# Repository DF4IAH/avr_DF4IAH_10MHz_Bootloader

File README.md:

# avr_DF4IAH_Bootloader

## GPS disciplined 10 MHz reference oscillator based on a (VC)TCXO
The project name for this device is __10 MHz-Ref.-Osc. V2.x__

That board is attached at the USB bus and receives power and does communication over it.
An optional LCD module can be connected to the I²C compatible bus for a stand-alone operation.

The author is Ulrich Habel (DF4IAH) with the idea having a low-cost and low-power device for a module to generate a 10 MHz signal at 3.3V TTL, that is adjusted to the GPS/Glonass satellite clock system. By this the local clock is kept in its boundaries to satisfy the long-term stability of the GPS/Glonass system. The negative aspect on it (I want to inform, also) with the use of a low power consuming VC-TCXO is, that the short-term variance is much higher than the variance of the devices using a temperature controlled oscillator like a rubidium lightwave controlled one.

### Contents of this repository
- __AVR ATmega 328P__: MPU containing a bootloader for programming the firmware itself via the USB interface by emulating an USBasp device 

- __Lattice LC4032V__: CPLD for containing a phase detection unit - source and binary

- __Eagle drawings__: oscillator and LCD - the schematics and boards for all variants of V2.x

### Additional information
The idea behind that project was to craft a local oscillator being in phase of the GPS clock system.
The device shall have a frequency and phase locked loop.
When the local frequency is trimmed to be equal to the reference GPS clock the phase locked loop gets in place of the frequency control.
Whenever the phase gets out of the secured boundaries, the system switches back to the frequency correction mode.
Due to its nature the device has to keep itself earnestly in the secured boundaries.
Only then the high quality stability of the GPS clock system can be delivered to the user.
For this reason when the local clock gets more out of balance and to one of its boundaries, a phase correction impulse is added to the local system to find the balance, again.
When still running a longer time this pulses are fine grained and the performance is very well for the user.
On the other hand when the GPS signals are poor, the almanac data old or the temperature variance at the VC-TCXO increasing, that local error-signal has to be corrected sometimes with sharp corrections.
So be warned to keep the device running in an air-locked container and a good GPS antenna position is a __must__ to get good results.

There are three different kinds of GPS units used by this project.
Each of them are utilizing the __MediaTek MT3333__ chipset, but each of the manufacturer is running its own configuration on it.
By this, some minor differences occur.
All of this GPS devices are able to track on GPS (western satellites) and Glonass/BeiDou (eastern satellites) signals.
Later at the works the author found out that the parallel processing of GPS and Glonass can result to interrupted functionality.
With NMEA programming the GPS device receives the command to ignore the Glonass signals but not all of them do honor that and start up tracking of all received signals.
The only work-around for this is to use a more selective GPS-antenna that filters out the Glonass signals away from the single GPS frequency.

The author has his reference clocks running for month without any problems, the firmware is stable - __use on your own risk, only!__

If you find this project nice you are welcomed to clone from it and run your optimizations or having a start point for a fresh project.

Any new modifications may result to harm this behavior.
Make your own decisions, be warned.

### Credits
I like to thank these following programmers and groups:

- __VUSB__ This code helped me to have USB communication on an ATmega, that does not support USB communication on its own.
All is done by interrupt software, many parts are assembly language based code.
Due to this nature all code in the bootloader as well as the firmware are very sensitive to changes on the code.
Only a very short interrupt time is allowed for the firmware avoiding the USB communication to fade out.
Find more about it: https://www.obdev.at/products/vusb/index.html

- __Wouter van Ooijen__ That person has reserved a valid USB address to be used by the community.
I like to thank him, that I am a part of this open source development community.

- __USBasp__ The base idea of the circuit is a reflection of this AVR programmer device.
The clou of it, it can communicate at the USB bus by itself: http://www.fischl.de/usbasp/

- __avrdude__ The bootloader code of avrdude gave ideas how to set-up a USB communication server.
The avrdude software can be found there: http://www.nongnu.org/avrdude/

- __HF-Messzwerg__ When the author got in contact with the team of this device, he started to learn about SMD soldering and USB communication in relation with an ATmega.
Communication is done with the help of an USB/serial converter.
More about that project can be found there: http://ukw-tagung.org/2016/preistraeger-2/

I wish you a nice experience with this product.
Fell free and enjoy it.

Cheers

Ulrich Habel  (DF4IAH)

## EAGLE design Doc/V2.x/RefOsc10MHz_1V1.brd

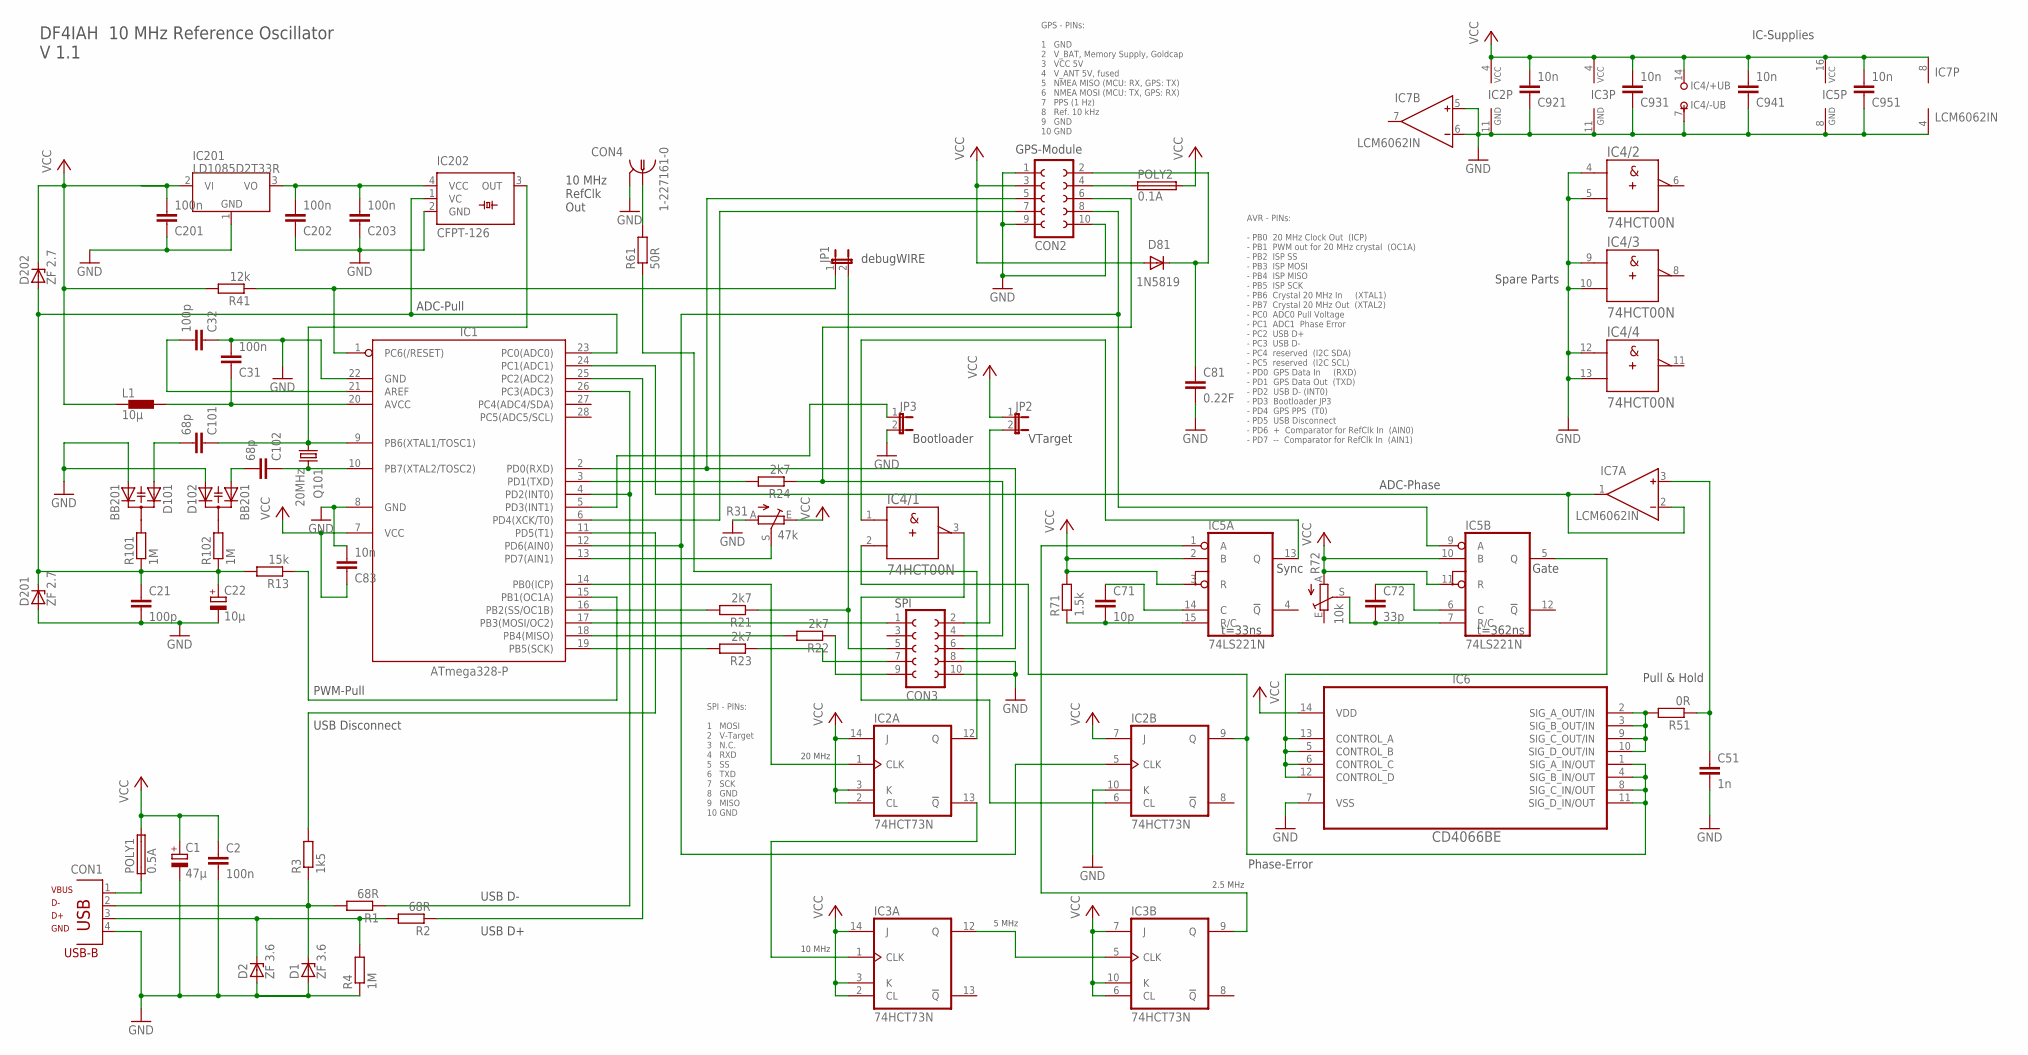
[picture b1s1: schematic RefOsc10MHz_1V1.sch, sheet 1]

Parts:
C1: 47µ; E2-4
C2, C31, C201, C202, C203: 100n; C5B3
C21, C32: 100p; C5B3
C22: 10µ; E2-4
C51: 1n; C5B3
C71: 10p; C5B3
C72: 33p; C5B3
C81: 0.22F; C5B7.2
C83, C921, C931, C941, C951: 10n; C5B3
C101, C102: 68p; C5B3
CON1: PN61729
CON2, CON3: FE05-2
CON4: 1-227161-0; AMP_227161
D1, D2: ZF 3.6; DO41Z10
D81: 1N5819; DO41-10
D101, D102: BB201; SOT23
D201, D202: ZF 2.7; DO41Z10
IC1: ATmega328-P; DIL28-3
IC2, IC3: 74HCT73N; DIL14
IC4: 74HCT00N; DIL14
IC5: 74LS221N; DIL16
IC6: CD4066BE; DIP254P762X508-14
IC7: LCM6062IN; DIL08
IC201: LD10853.3; TO220V
IC202: CFPT-126; SM77H
JP1, JP2, JP3: JP1E; JP1
L1: 10µ; BL01RN1A
POLY1: 0.5A; TE5
POLY2: 0.1A; TE5
Q101: 20MHz; HC49U70
R1, R2: 68R; 0204/7
R3: 1k5; 0204/7
R4, R101, R102: 1M; 0204/7
R13: 15k; 0204/7
R21, R22, R23, R24: 2k7; 0204/7
R31: 47k; S64YW
R41: 12k; 0204/7
R51: 0R; 0204/7
R61: 50R; 0204/7
R71: 1.5k; 0204/7
R72: 10k; S64YW

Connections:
GND: C1.-, C2.2, C21.2, C22.-, C31.2, C32.1, C51.2, C81.2, C83.2, C201.1, C202.1, C203.1, C921.1, C931.1, C941.1, C951.1, CON1.4, CON2.1, CON2.9, CON2.10, CON3.8, CON3.10, CON4.2, D1.A, D2.A, D101.2 (A2), D102.1 (A1), D201.A, IC1.8 (GND), IC1.22 (GND), IC2.10 (K), IC2.11 (GND), IC3.11 (GND), IC4.4 (A), IC4.5 (B), IC4.7 (-UB), IC4.9 (A), IC4.10 (B), IC4.12 (A), IC4.13 (B), IC5.8 (GND), IC6.7 (VSS), IC7.4 (V-), IC7.5 (IN+), IC7.6 (IN-), IC201.1 (GND), IC202.2 (GND), JP3.2, R4.1, R31.A
N3V3: C202.2, C203.2, IC201.3 (VO), IC202.4 (VCC)
unnamed: C101.1, IC1.9 (PB6(XTAL1/TOSC1)), IC202.3 (OUT), Q101.1
unnamed: C102.1, IC1.10 (PB7(XTAL2/TOSC2)), Q101.2
unnamed: D102.3 (C), R102.2
unnamed: C101.2, D101.1 (A1)
unnamed: C21.1, C22.+, D201.C, D202.A, IC1.23 (PC0(ADC0)), IC202.1 (VC), R13.2, R101.1, R102.1
unnamed: CON1.2, D1.C, R1.2, R3.1
unnamed: CON1.3, D2.C, R2.2, R4.2
unnamed: IC1.4 (PD2(INT0)), IC1.26 (PC3(ADC3)), R1.1
unnamed: IC1.25 (PC2(ADC2)), R2.1
unnamed: IC1.16 (PB2(SS/OC1B)), R21.2
unnamed: CON3.1, IC1.17 (PB3(MOSI/OC2))
unnamed: IC1.19 (PB5(SCK)), R23.2
unnamed: C31.1, IC1.20 (AVCC), L1.2
unnamed: IC1.18 (PB4(MISO)), R22.2
unnamed: CON3.5, JP1.2, R21.1
unnamed: CON3.9, R22.1
unnamed: CON3.7, R23.1
unnamed: IC1.3 (PD1(TXD)), R24.2
unnamed: IC1.14 (PB0(ICP)), IC2.1 (CLK)
unnamed: CON2.5, CON3.6, IC1.2 (PD0(RXD))
unnamed: CON2.6, CON3.4, R24.1
unnamed: IC1.1 (PC6(/RESET)), JP1.1, R41.1
unnamed: CON3.2, JP2.2
unnamed: CON2.8, IC1.12 (PD6(AIN0)), IC2.5 (CLK), IC5.9 (A)
unnamed: IC1.13 (PD7(AIN1)), R31.S
unnamed: IC1.15 (PB1(OC1A)), R13.1
unnamed: C32.2, IC1.21 (AREF)
unnamed: IC1.5 (PD3(INT1)), JP3.1
unnamed: C102.2, D102.2 (A2)
unnamed: D101.3 (C), R101.2
unnamed: IC2.12 (Q), R61.1
unnamed: IC2.9 (Q), IC4.2 (B), IC6.1 (SIG_A_IN/OUT), IC6.4 (SIG_B_IN/OUT), IC6.8 (SIG_C_IN/OUT), IC6.11 (SIG_D_IN/OUT)
unnamed: IC6.2 (SIG_A_OUT/IN), IC6.3 (SIG_B_OUT/IN), IC6.9 (SIG_C_OUT/IN), IC6.10 (SIG_D_OUT/IN), R51.2
unnamed: C51.1, IC7.3 (IN+), R51.1
unnamed: IC2.6 (CL), IC4.3 (Y)
unnamed: IC5.5 (Q), IC6.5 (CONTROL_B), IC6.6 (CONTROL_C), IC6.12 (CONTROL_D), IC6.13 (CONTROL_A)
unnamed: IC1.24 (PC1(ADC1)), IC7.1 (OUT), IC7.2 (IN-)
unnamed: CON1.1, POLY1.1
unnamed: CON2.4, POLY2.1
unnamed: CON2.7, IC1.6 (PD4(XCK/T0))
unnamed: IC1.11 (PD5(T1)), R3.2
unnamed: CON4.1, R61.2
unnamed: IC4.1 (A), IC5.13 (Q)
unnamed: C72.2, IC5.7 (R/C), R72.S
unnamed: C72.1, IC5.6 (C)
unnamed: IC3.9 (Q), IC5.1 (A)
unnamed: C71.2, IC5.15 (R/C), R71.1
unnamed: C71.1, IC5.14 (C)
unnamed: IC2.13 (!Q), IC3.1 (CLK)
unnamed: IC3.5 (CLK), IC3.12 (Q)
unnamed: C81.1, CON2.2, D81.C
VCC: C1.+, C2.1, C83.1, C201.2, C921.2, C931.2, C941.2, C951.2, CON2.3, D81.A, D202.C, IC1.7 (VCC), IC2.2 (CL), IC2.3 (K), IC2.4 (VCC), IC2.7 (J), IC2.14 (J), IC3.2 (CL), IC3.3 (K), IC3.4 (VCC), IC3.6 (CL), IC3.7 (J), IC3.10 (K), IC3.14 (J), IC4.14 (+UB), IC5.2 (B), IC5.3 (R), IC5.10 (B), IC5.11 (R), IC5.16 (VCC), IC6.14 (VDD), IC7.8 (V+), IC201.2 (VI), JP2.1, L1.1, POLY1.2, POLY2.2, R31.E, R41.2, R71.2, R72.A

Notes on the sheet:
VTarget
debugWIRE
VBUS
GND
USB-B
AVR - PINs: - PB0 20 MHz Clock Out (ICP) - PB1 PWM out for 20 MHz crystal (OC1A) - PB2 ISP SS - PB3 ISP MOSI - PB4 ISP MISO - PB5 ISP SCK - PB6 Crystal 20 MHz In (XTAL1) - PB7 Crystal 20 MHz Out (XTAL2) - PC0 ADC0 Pull Voltage - PC1 ADC1 Phase Error - PC2 USB D+ - PC3 USB D- - PC4 reserved (I2C SDA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
SPI
10 MHz RefClk Out
Bootloader
Phase-Error
Gate
GPS-Module
GPS - PINs: 1 GND 2 V_BAT, Memory Supply, Goldcap 3 VCC 5V 4 V_ANT 5V, fused 5 NMEA MISO (MCU: RX, GPS: TX) 6 NMEA MOSI (MCU: TX, GPS: RX) 7 PPS (1 Hz) 8 Ref. 10 kHz 9 GND 10 GND
Pull & Hold
ADC-Phase
PWM-Pull
ADC-Pull
Sync
t=33ns
t=362ns
IC-Supplies
Spare Parts
20 MHz
10 MHz
5 MHz
2.5 MHz
DF4IAH 10 MHz Reference Oscillator V 1.1
USB Disconnect
USB D-
USB D+
SPI - PINs: 1 MOSI 2 V-Target 3 N.C. 4 RXD 5 SS 6 TXD 7 SCK 8 GND 9 MISO 10 GND

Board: 2 copper layers, 64 parts (0 on the bottom side), 54 nets, no tracks yet.

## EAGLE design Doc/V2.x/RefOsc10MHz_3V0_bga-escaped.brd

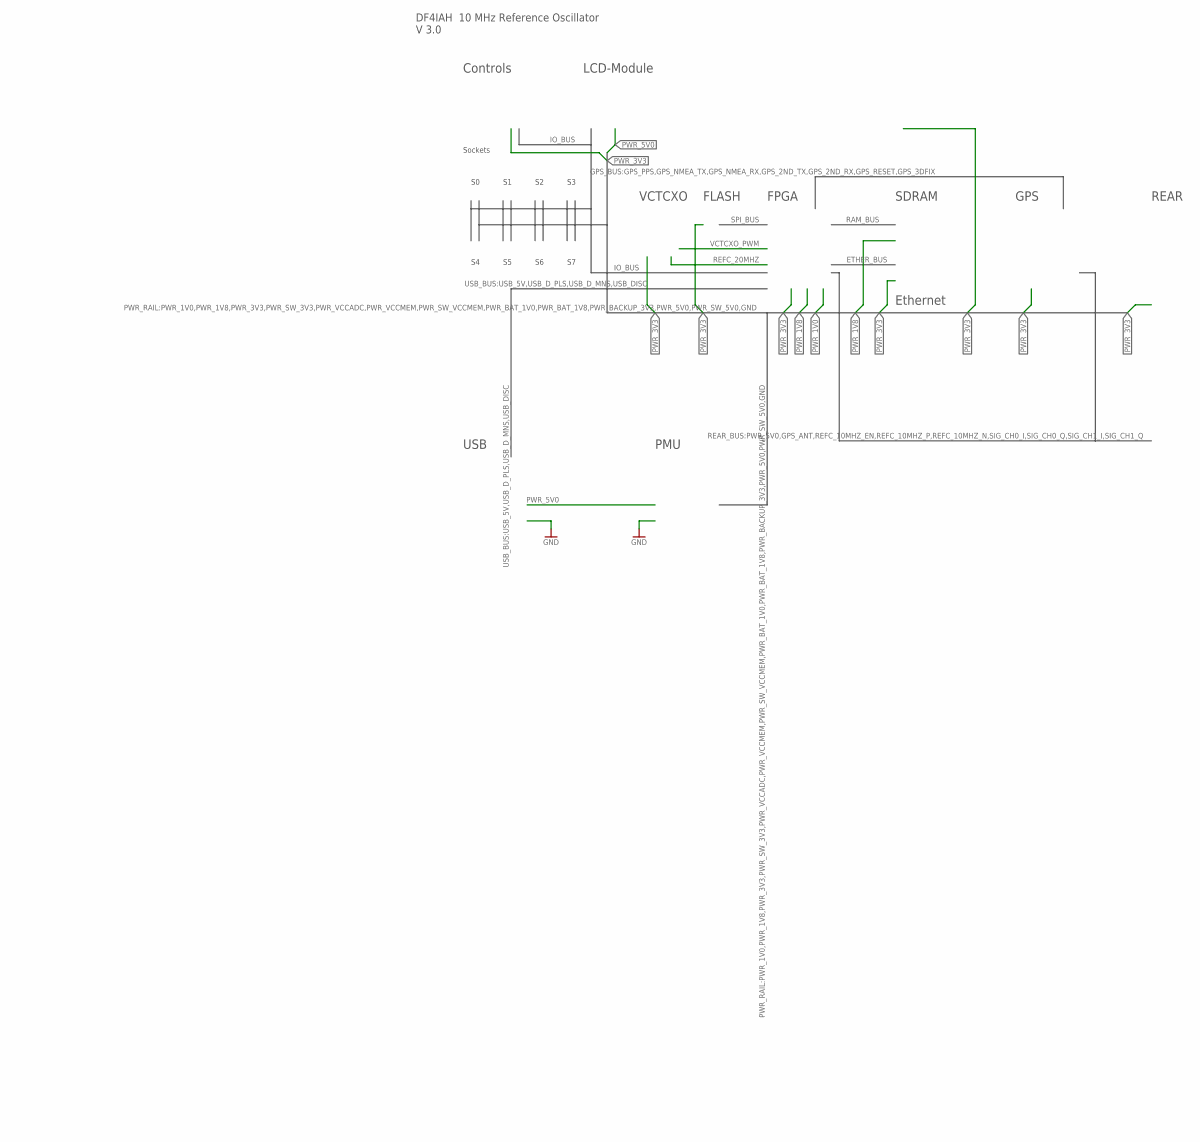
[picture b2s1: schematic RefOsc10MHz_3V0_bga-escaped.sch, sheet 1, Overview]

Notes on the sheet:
VCTCXO
FPGA
GPS
REAR
LCD-Module
Controls
USB
PMU
Sockets
SDRAM
Ethernet
FLASH
DF4IAH 10 MHz Reference Oscillator V 3.0

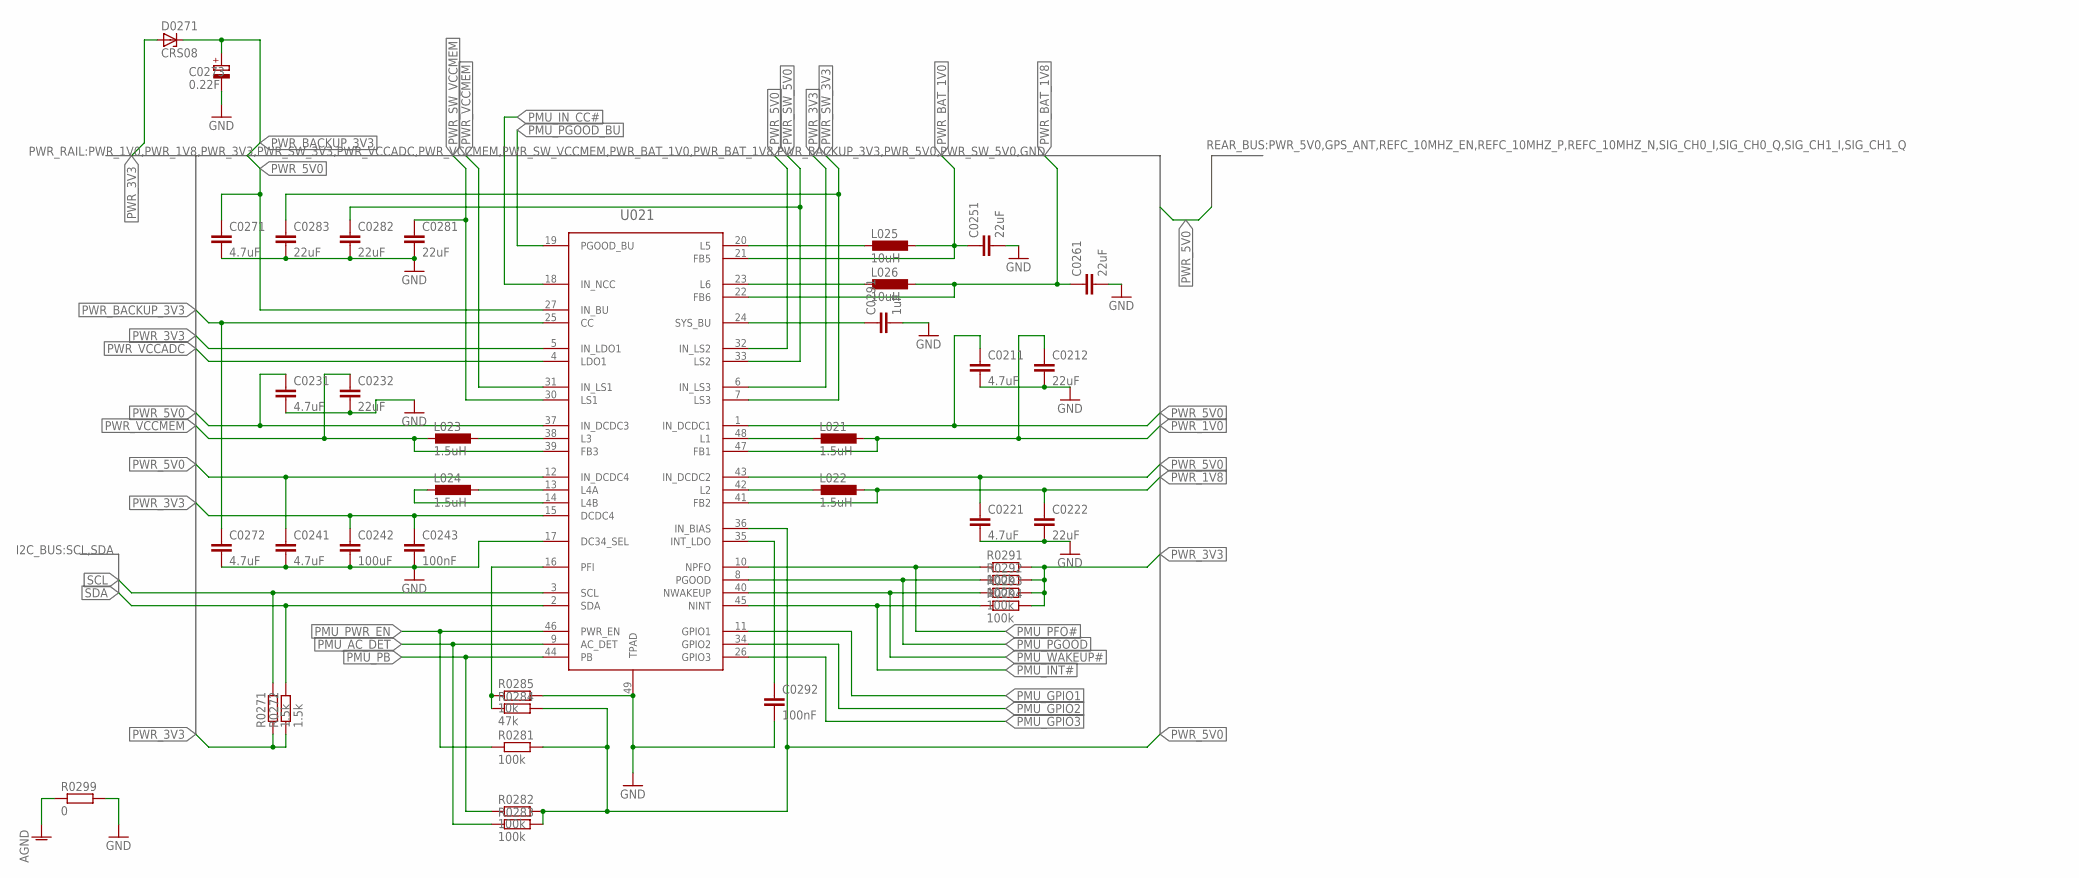
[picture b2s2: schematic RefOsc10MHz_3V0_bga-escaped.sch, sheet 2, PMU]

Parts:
C0211, C0221, C0231, C0241, C0271, C0272: 4.7uF; C0805
C0212, C0222, C0232, C0251, C0261, C0281, C0282, C0283: 22uF; C0805
C0242: 100uF; C0805
C0243, C0292: 100nF; C0805
C0273: 0.22F; PANASONIC_C
C0291: 1uF; C0805
D0271: CRS08; SOT23
L021, L022, L023, L024: 1.5uH; L1812
L025, L026: 10uH; L1812
R0271, R0272: 1.5k; R0603
R0281, R0282, R0283, R0291, R0292, R0293, R0294: 100k; R0603
R0284: 47k; R0603
R0285: 10k; R0603
R0299: 0; R0805
U021: TPS65218; QFP50P900X900X120-49N2

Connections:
AGND: R0299.1; also elsewhere on the board
GND: C0211.2, C0212.2, C0221.2, C0222.2, C0231.2, C0232.2, C0241.2, C0242.2, C0243.2, C0251.2, C0261.2, C0271.2, C0272.2, C0273.-, C0281.2, C0282.2, C0283.2, C0291.2, C0292.2, R0285.2, R0299.2, U021.17 (DC34_SEL), U021.49 (TPAD); also elsewhere on the board
L1: L021.2, U021.48 (L1)
L2: L022.2, U021.42 (L2)
L3: L023.1, U021.38 (L3)
L4A: L024.1, U021.13 (L4A)
L4B: L024.2, U021.14 (L4B)
L5: L025.2, U021.20 (L5)
L6: L026.2, U021.23 (L6)
unnamed: C0292.1, U021.35 (INT_LDO)
unnamed: R0284.1, R0285.1, U021.16 (PFI)
PMU_AC_DET: R0283.1, U021.9 (AC_DET)
PMU_GPIO1: U021.11 (GPIO1); also elsewhere on the board
PMU_GPIO2: U021.34 (GPIO2); also elsewhere on the board
PMU_GPIO3: U021.26 (GPIO3); also elsewhere on the board
PMU_INT#: R0294.1, U021.45 (NINT); also elsewhere on the board
PMU_IN_CC#: U021.18 (IN_NCC); also elsewhere on the board
PMU_PB: R0282.1, U021.44 (PB)
PMU_PFO#: R0291.1, U021.10 (NPFO); also elsewhere on the board
PMU_PGOOD: R0292.1, U021.8 (PGOOD); also elsewhere on the board
PMU_PGOOD_BU: U021.19 (PGOOD_BU); also elsewhere on the board
PMU_PWR_EN: R0281.1, U021.46 (PWR_EN); also elsewhere on the board
PMU_WAKEUP#: R0293.1, U021.40 (NWAKEUP); also elsewhere on the board
PWR_1V0: C0212.1, L021.1, U021.47 (FB1); also elsewhere on the board
PWR_1V8: C0222.1, L022.1, U021.41 (FB2); also elsewhere on the board
PWR_3V3: C0242.1, C0243.1, D0271.1 (A), R0271.1, R0272.1, R0291.2, R0292.2, R0293.2, R0294.2, U021.5 (IN_LDO1), U021.6 (IN_LS3), U021.15 (DCDC4); also elsewhere on the board
PWR_5V0: C0211.1, C0221.1, C0231.1, C0241.1, C0271.1, R0281.2, R0282.2, R0283.2, R0284.2, U021.1 (IN_DCDC1), U021.12 (IN_DCDC4), U021.27 (IN_BU), U021.32 (IN_LS2), U021.36 (IN_BIAS), U021.37 (IN_DCDC3), U021.43 (IN_DCDC2); also elsewhere on the board
PWR_BACKUP_3V3: C0272.1, C0273.+, D0271.3 (C), U021.25 (CC); also elsewhere on the board
PWR_BAT_1V0: C0251.1, L025.1, U021.21 (FB5)
PWR_BAT_1V8: C0261.1, L026.1, U021.22 (FB6); also elsewhere on the board
PWR_SW_3V3: C0283.1, U021.7 (LS3)
PWR_SW_5V0: C0282.1, U021.33 (LS2)
PWR_SW_VCCMEM: C0281.1, U021.30 (LS1)
PWR_VCCADC: U021.4 (LDO1); also elsewhere on the board
PWR_VCCMEM: C0232.1, L023.2, U021.31 (IN_LS1), U021.39 (FB3)
SCL: R0271.2, U021.3 (SCL); also elsewhere on the board
SDA: R0272.2, U021.2 (SDA); also elsewhere on the board
SYS_BU: C0291.1, U021.24 (SYS_BU)

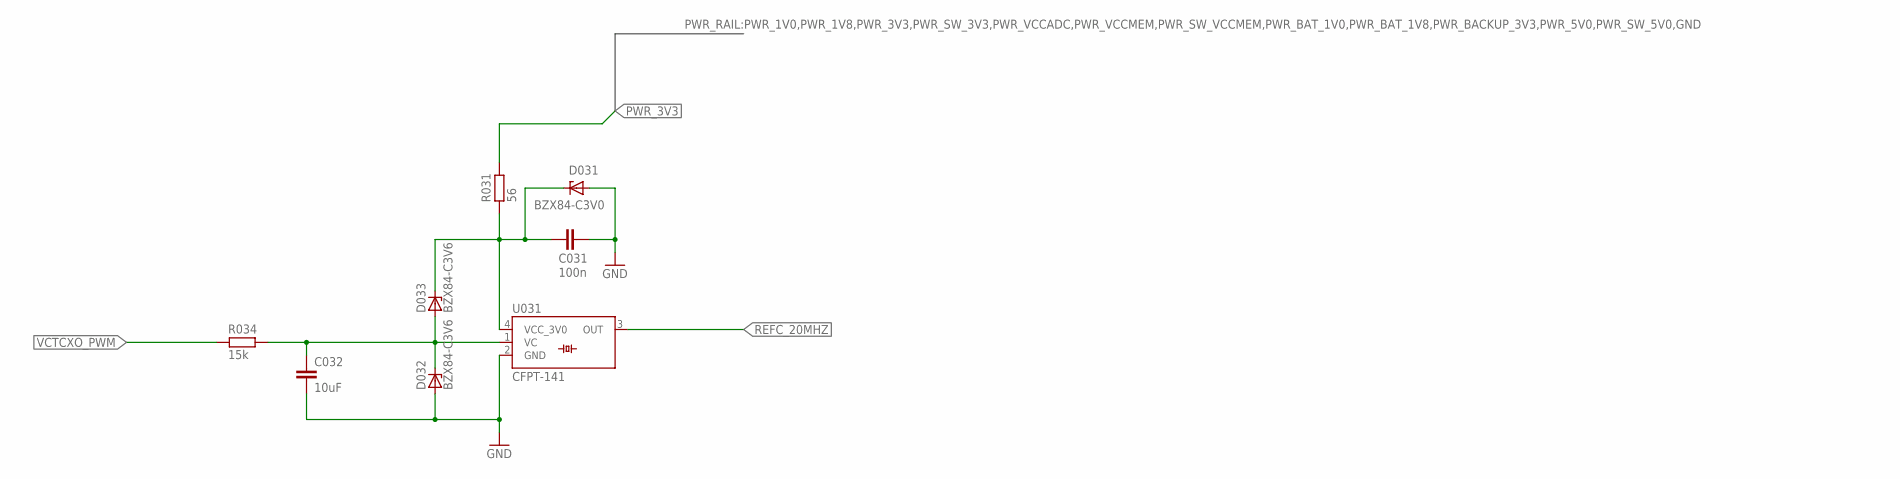
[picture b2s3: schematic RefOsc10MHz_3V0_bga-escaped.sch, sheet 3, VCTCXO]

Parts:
C031: 100n; C0805
C032: 10uF; C0805
D031: BZX84-C3V0; TO236
D032, D033: BZX84-C3V6; TO236
R031: 56; R0805
R034: 15k; R0603
U031: CFPT-141

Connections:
GND: C031.2, C032.2, D031.A, D032.A, U031.2 (GND); also elsewhere on the board
PWR_3V3: R031.1; also elsewhere on the board
PWR_VCTCXO_3V0: C031.1, D031.C, D033.C, R031.2, U031.4 (VCC_3V0)
REFC_20MHZ: U031.3 (OUT); also elsewhere on the board
VCTCXO_PWM: R034.2; also elsewhere on the board
VCTCXO_VC_IN: C032.1, D032.C, D033.A, R034.1, U031.1 (VC)

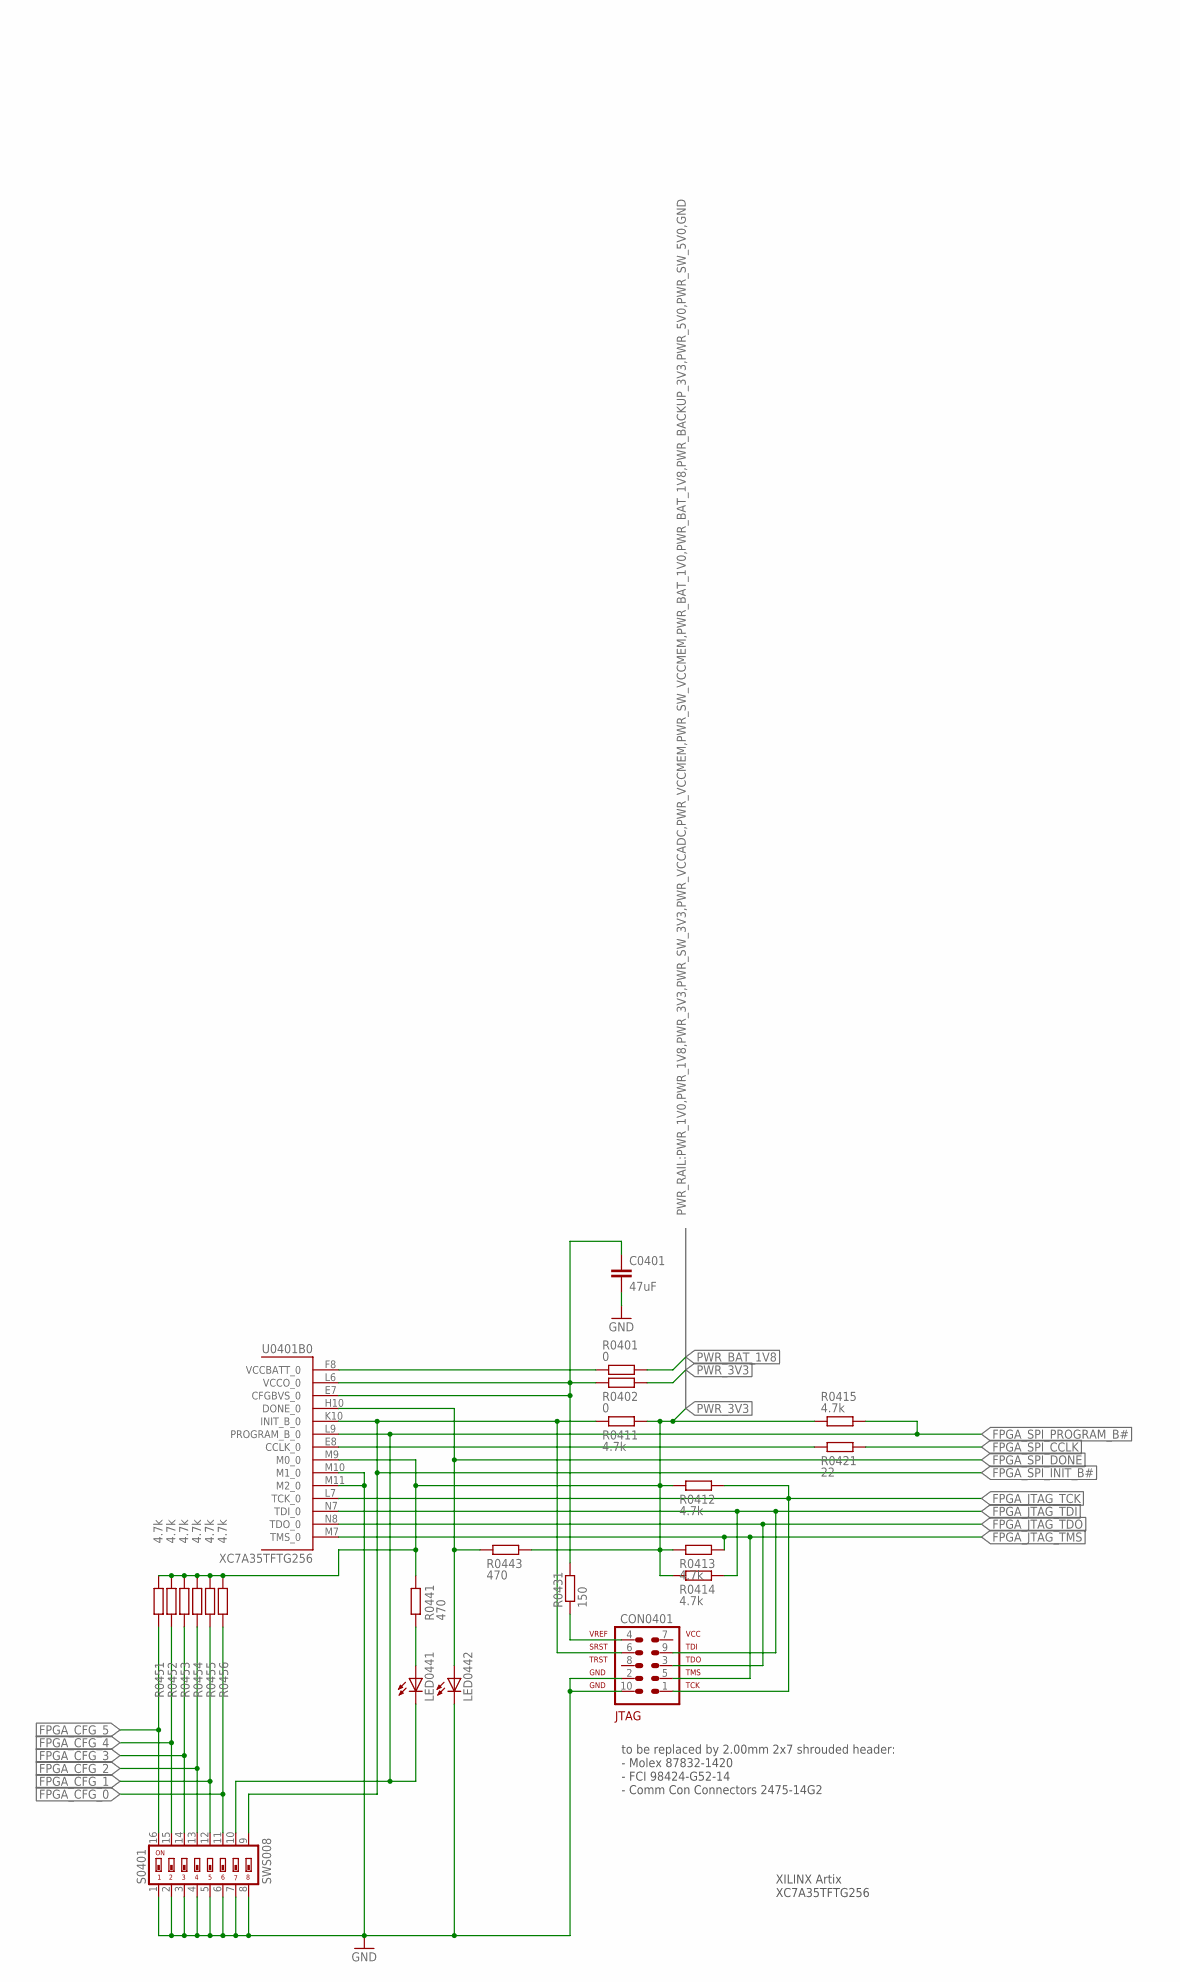
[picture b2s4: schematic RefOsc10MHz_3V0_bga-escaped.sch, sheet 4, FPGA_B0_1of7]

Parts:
C0401: 47uF; C0805
CON0401: AVR-JTAG-10SMD; 2X5SMD
LED0441, LED0442: LED; SMARTLED-TTW
R0401, R0402: 0; R0402
R0411, R0412, R0413, R0414, R0415, R0451, R0452, R0453, R0454, R0455, R0456: 4.7k; R0805
R0421: 22; R0805
R0431: 150; R0805
R0441, R0443: 470; R0805
S0401: SWS008; SMS-008
U0401: XC7A35TFTG256; FTG256_0MM4

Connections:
FPGA_CCLK_INTERN: R0421.1, U0401.E8 (CCLK_0)
FPGA_CFG_0: R0456.1, S0401.11; also elsewhere on the board
FPGA_CFG_1: R0455.1, S0401.12; also elsewhere on the board
FPGA_CFG_2: R0454.1, S0401.13; also elsewhere on the board
FPGA_CFG_3: R0453.1, S0401.14; also elsewhere on the board
FPGA_CFG_4: R0452.1, S0401.15; also elsewhere on the board
FPGA_CFG_5: R0451.1, S0401.16; also elsewhere on the board
FPGA_JTAG_TCK: CON0401.1, R0412.2, U0401.L7 (TCK_0)
FPGA_JTAG_TDI: CON0401.9, R0414.2, U0401.N7 (TDI_0)
FPGA_JTAG_TDO: CON0401.3, U0401.N8 (TDO_0)
FPGA_JTAG_TMS: CON0401.5, R0413.2, U0401.M7 (TMS_0)
FPGA_SPI_CCLK: R0421.2; also elsewhere on the board
FPGA_SPI_DONE: LED0442.A@1 (A), R0443.1, U0401.H10 (DONE_0)
FPGA_SPI_INIT_B#: CON0401.6, R0411.1, S0401.9, U0401.K10 (INIT_B_0)
FPGA_SPI_PROGRAM_B#: LED0441.C@1 (C), R0415.2, S0401.10, U0401.L9 (PROGRAM_B_0)
FPGA_VCCBATT: R0401.1, U0401.F8 (VCCBATT_0)
FPGA_VCCO_0: C0401.1, R0402.1, R0431.2, U0401.E7 (CFGBVS_0), U0401.L6 (VCCO_0)
GND: C0401.2, CON0401.2, CON0401.10, LED0442.C@1 (C), S0401.1, S0401.2, S0401.3, S0401.4, S0401.5, S0401.6, S0401.7, S0401.8, U0401.M10 (M1_0), U0401.M11 (M2_0); also elsewhere on the board
unnamed: LED0441.A@1 (A), R0441.1
unnamed: CON0401.4, R0431.1
PWR_3V3: R0402.2, R0411.2, R0412.1, R0413.1, R0414.1, R0415.1, R0441.2, R0443.2, R0451.2, R0452.2, R0453.2, R0454.2, R0455.2, R0456.2, U0401.M9 (M0_0); also elsewhere on the board
PWR_BAT_1V8: R0401.2; also elsewhere on the board

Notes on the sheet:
XILINX Artix XC7A35TFTG256
to be replaced by 2.00mm 2x7 shrouded header: - Molex 87832-1420 - FCI 98424-G52-14 - Comm Con Connectors 2475-14G2

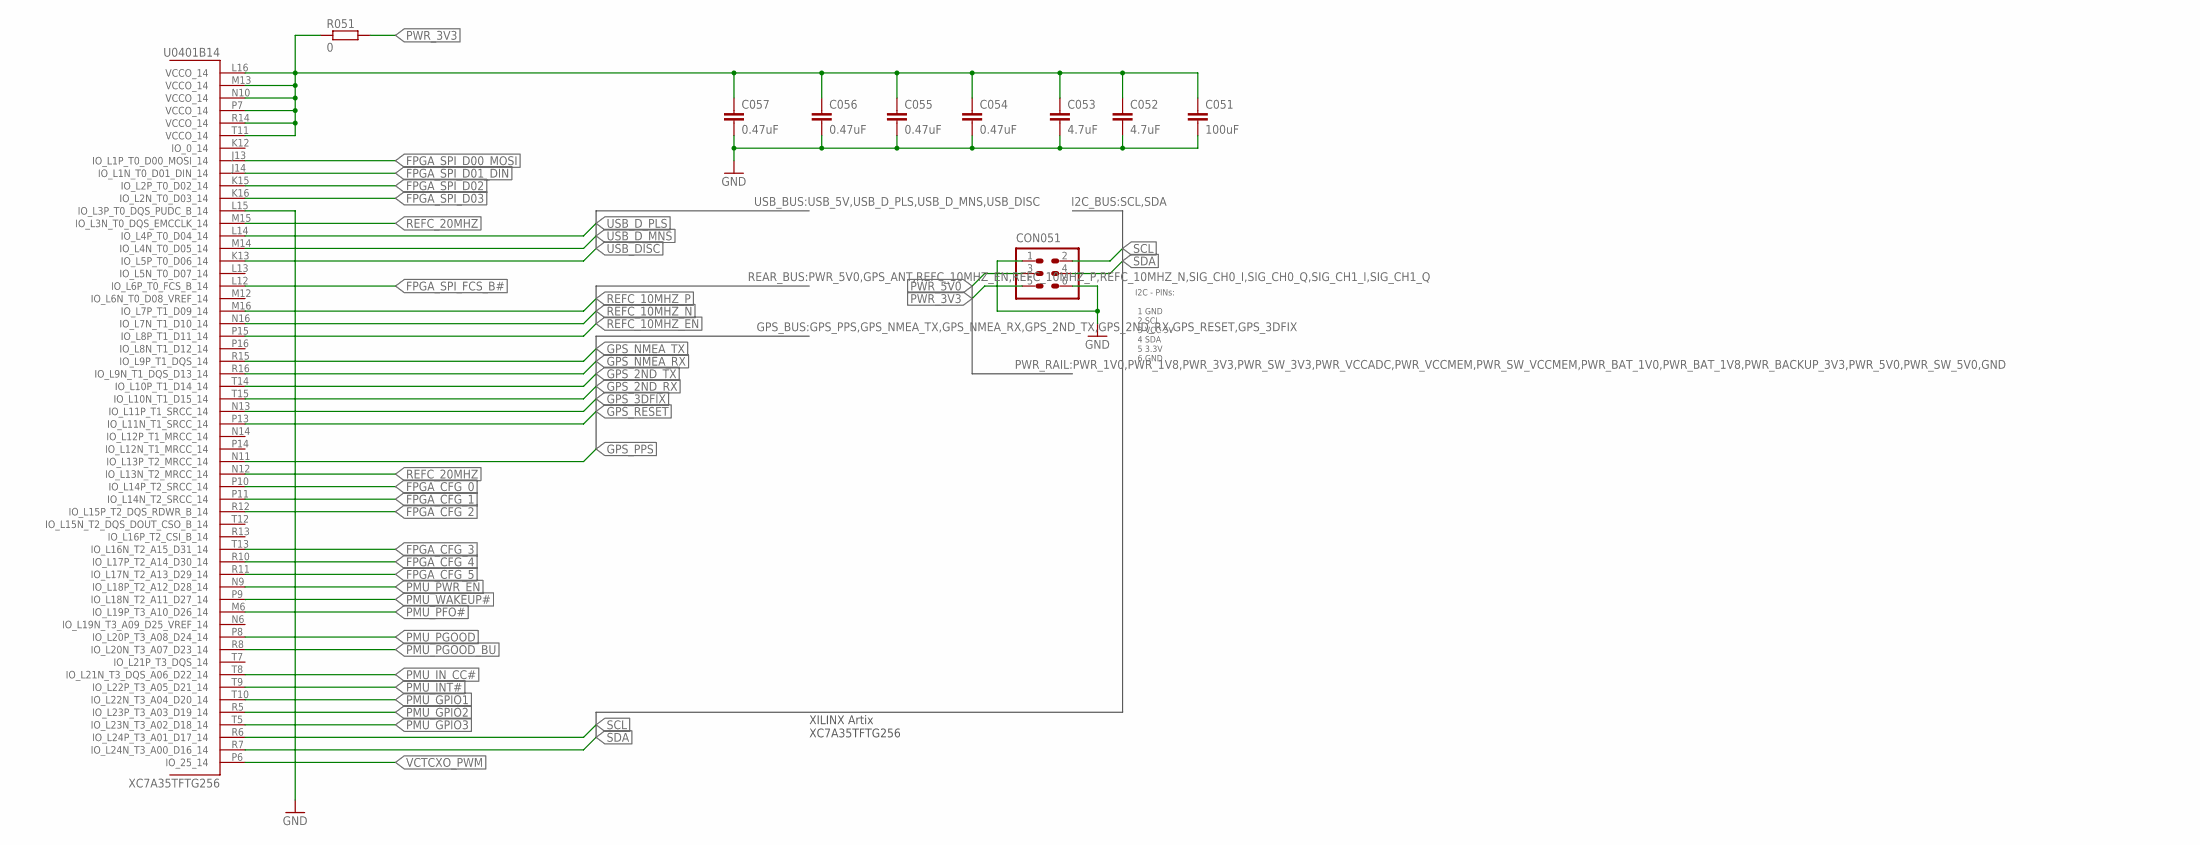
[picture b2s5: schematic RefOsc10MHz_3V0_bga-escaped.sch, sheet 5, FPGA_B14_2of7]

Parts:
C051: 100uF; C1206
C052, C053: 4.7uF; C0402
C054, C055, C056, C057: 0.47uF; C0402
CON051: HEADER-2X3SMD; 2X03SMD
R051: 0; R0402
U0401: XC7A35TFTG256; FTG256_0MM4

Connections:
FPGA_CFG_0: U0401.P10 (IO_L14P_T2_SRCC_14); also elsewhere on the board
FPGA_CFG_1: U0401.P11 (IO_L14N_T2_SRCC_14); also elsewhere on the board
FPGA_CFG_2: U0401.R12 (IO_L15P_T2_DQS_RDWR_B_14); also elsewhere on the board
FPGA_CFG_3: U0401.T13 (IO_L16N_T2_A15_D31_14); also elsewhere on the board
FPGA_CFG_4: U0401.R10 (IO_L17P_T2_A14_D30_14); also elsewhere on the board
FPGA_CFG_5: U0401.R11 (IO_L17N_T2_A13_D29_14); also elsewhere on the board
FPGA_SPI_D00_MOSI: U0401.J13 (IO_L1P_T0_D00_MOSI_14); also elsewhere on the board
FPGA_SPI_D01_DIN: U0401.J14 (IO_L1N_T0_D01_DIN_14); also elsewhere on the board
FPGA_SPI_D02: U0401.K15 (IO_L2P_T0_D02_14); also elsewhere on the board
FPGA_SPI_D03: U0401.K16 (IO_L2N_T0_D03_14); also elsewhere on the board
FPGA_SPI_FCS_B#: U0401.L12 (IO_L6P_T0_FCS_B_14); also elsewhere on the board
FPGA_VCCO_14: C051.1, C052.1, C053.1, C054.1, C055.1, C056.1, C057.1, R051.1, U0401.L16 (VCCO_14), U0401.M13 (VCCO_14), U0401.N10 (VCCO_14), U0401.P7 (VCCO_14), U0401.R14 (VCCO_14), U0401.T11 (VCCO_14)
GND: C051.2, C052.2, C053.2, C054.2, C055.2, C056.2, C057.2, CON051.1, CON051.6, U0401.L15 (IO_L3P_T0_DQS_PUDC_B_14); also elsewhere on the board
GPS_2ND_RX: U0401.T15 (IO_L10N_T1_D15_14)
GPS_2ND_TX: U0401.T14 (IO_L10P_T1_D14_14)
GPS_3DFIX: U0401.N13 (IO_L11P_T1_SRCC_14)
GPS_NMEA_RX: U0401.R16 (IO_L9N_T1_DQS_D13_14); also elsewhere on the board
GPS_NMEA_TX: U0401.R15 (IO_L9P_T1_DQS_14); also elsewhere on the board
GPS_PPS: U0401.N11 (IO_L13P_T2_MRCC_14); also elsewhere on the board
GPS_RESET: U0401.P13 (IO_L11N_T1_SRCC_14); also elsewhere on the board
PMU_GPIO1: U0401.T10 (IO_L22N_T3_A04_D20_14); also elsewhere on the board
PMU_GPIO2: U0401.R5 (IO_L23P_T3_A03_D19_14); also elsewhere on the board
PMU_GPIO3: U0401.T5 (IO_L23N_T3_A02_D18_14); also elsewhere on the board
PMU_INT#: U0401.T9 (IO_L22P_T3_A05_D21_14); also elsewhere on the board
PMU_IN_CC#: U0401.T8 (IO_L21N_T3_DQS_A06_D22_14); also elsewhere on the board
PMU_PFO#: U0401.M6 (IO_L19P_T3_A10_D26_14); also elsewhere on the board
PMU_PGOOD: U0401.P8 (IO_L20P_T3_A08_D24_14); also elsewhere on the board
PMU_PGOOD_BU: U0401.R8 (IO_L20N_T3_A07_D23_14); also elsewhere on the board
PMU_PWR_EN: U0401.N9 (IO_L18P_T2_A12_D28_14); also elsewhere on the board
PMU_WAKEUP#: U0401.P9 (IO_L18N_T2_A11_D27_14); also elsewhere on the board
PWR_3V3: CON051.5, R051.2; also elsewhere on the board
PWR_5V0: CON051.3; also elsewhere on the board
REFC_10MHZ_EN: U0401.P15 (IO_L8P_T1_D11_14); also elsewhere on the board
REFC_10MHZ_N: U0401.N16 (IO_L7N_T1_D10_14); also elsewhere on the board
REFC_10MHZ_P: U0401.M16 (IO_L7P_T1_D09_14); also elsewhere on the board
REFC_20MHZ: U0401.M15 (IO_L3N_T0_DQS_EMCCLK_14), U0401.N12 (IO_L13N_T2_MRCC_14); also elsewhere on the board
SCL: CON051.2, U0401.R6 (IO_L24P_T3_A01_D17_14); also elsewhere on the board
SDA: CON051.4, U0401.R7 (IO_L24N_T3_A00_D16_14); also elsewhere on the board
USB_DISC: U0401.K13 (IO_L5P_T0_D06_14); also elsewhere on the board
USB_D_MNS: U0401.M14 (IO_L4N_T0_D05_14); also elsewhere on the board
USB_D_PLS: U0401.L14 (IO_L4P_T0_D04_14); also elsewhere on the board
VCTCXO_PWM: U0401.P6 (IO_25_14); also elsewhere on the board

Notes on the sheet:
I2C - PINs: 1 GND 2 SCL 3 VCC 5V 4 SDA 5 3.3V 6 GND
XILINX Artix XC7A35TFTG256

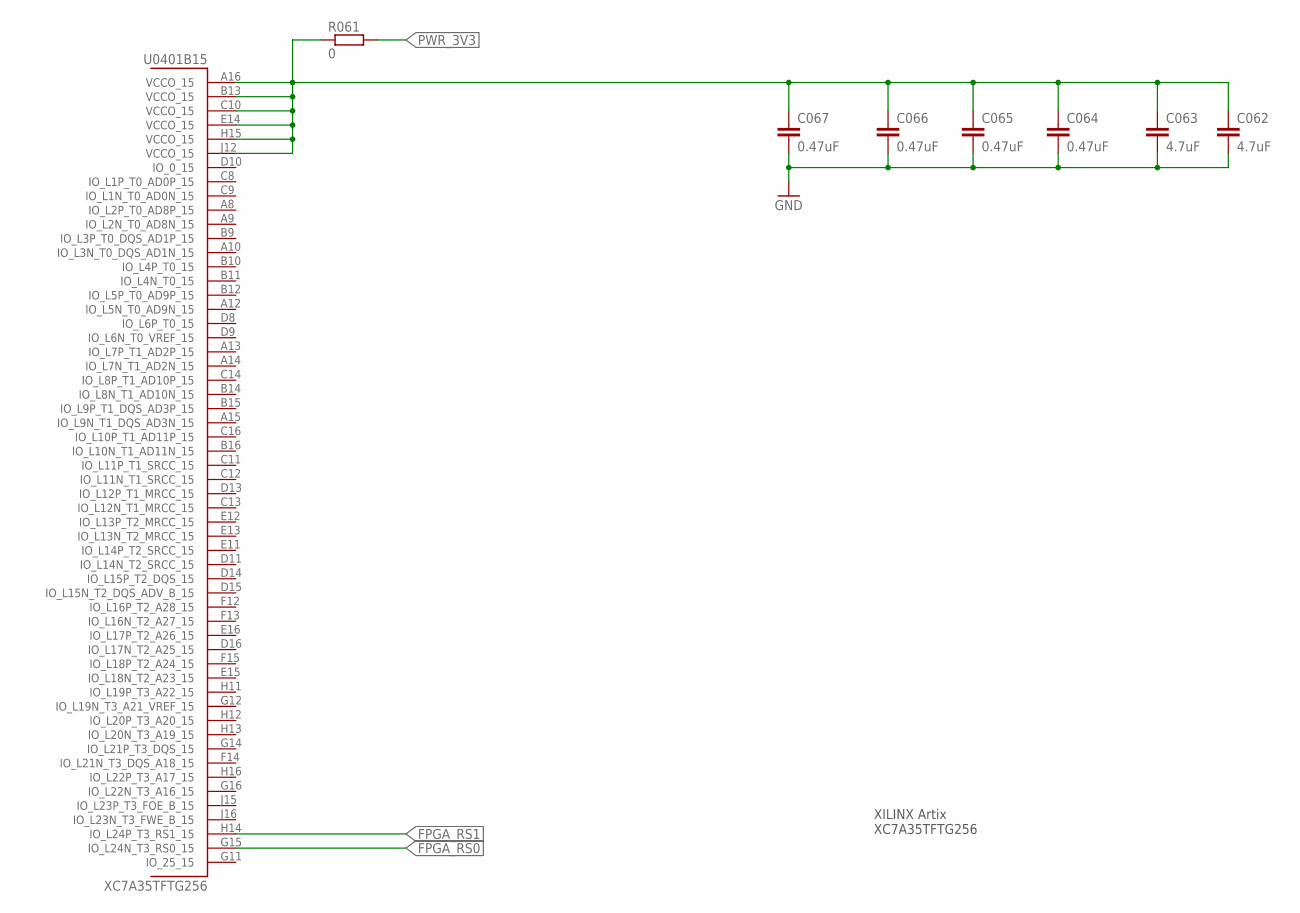
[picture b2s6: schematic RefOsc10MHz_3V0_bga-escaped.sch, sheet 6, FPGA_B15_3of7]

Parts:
C062, C063: 4.7uF; C0402
C064, C065, C066, C067: 0.47uF; C0402
R061: 0; R0402
U0401: XC7A35TFTG256; FTG256_0MM4

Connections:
FPGA_RS0: U0401.G15 (IO_L24N_T3_RS0_15)
FPGA_RS1: U0401.H14 (IO_L24P_T3_RS1_15)
FPGA_VCCO_15: C062.1, C063.1, C064.1, C065.1, C066.1, C067.1, R061.1, U0401.A16 (VCCO_15), U0401.B13 (VCCO_15), U0401.C10 (VCCO_15), U0401.E14 (VCCO_15), U0401.H15 (VCCO_15), U0401.J12 (VCCO_15)
GND: C062.2, C063.2, C064.2, C065.2, C066.2, C067.2; also elsewhere on the board
PWR_3V3: R061.2; also elsewhere on the board

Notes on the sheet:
XILINX Artix XC7A35TFTG256
